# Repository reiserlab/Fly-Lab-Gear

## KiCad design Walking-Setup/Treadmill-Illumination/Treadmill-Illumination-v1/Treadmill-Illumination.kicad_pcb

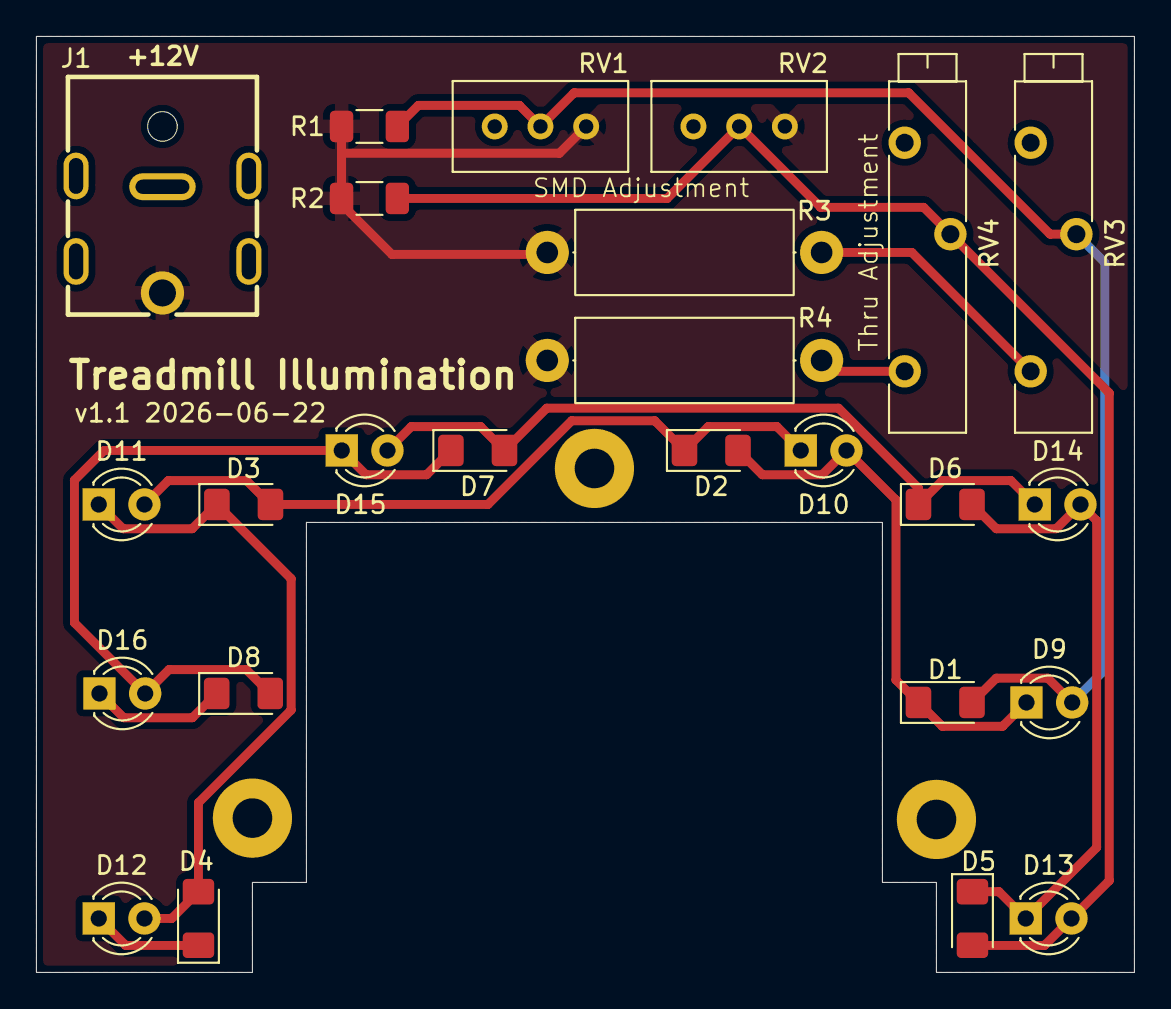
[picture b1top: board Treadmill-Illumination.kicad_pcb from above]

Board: 2 copper layers, 61.0 x 52.0 mm, 28 parts (0 on the bottom side), 12 nets.

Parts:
D1, D2, D3, D4, D5, D6, D7, D8: LED; LED_1206_3216Metric_Pad1.42x1.75mm_HandSolder
D9, D10, D11, D12, D13, D14, D15, D16: LED; LED_D3.0mm
H1, H2, H3: MountingHole_Pad; MountingHole_2.2mm_M2_Pad
J1: Barrel_Jack_MountingPin; DC-IN-TH_DC-053D-20A
R1, R2: 1k; R_1206_3216Metric_Pad1.30x1.75mm_HandSolder
R3, R4: 120; R_Axial_DIN0414_L11.9mm_D4.5mm_P15.24mm_Horizontal
RV1, RV2: R_Potentiometer; Potentiometer_Bourns_3386C_Horizontal
RV3, RV4: R_Potentiometer; Potentiometer_Bourns_3005_Horizontal

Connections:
+12V: J1.1, R1.1, R2.1, R3.1, R4.1, RV1.1, RV2.1
GND: D4.1 (K), D8.1 (K), D12.1 (K), D16.1 (K), H1.1 (1_1), H2.1 (1_1), H3.1 (1_1), J1.2, RV1.3, RV2.3, RV3.3, RV4.3
unnamed: D1.2 (A), D9.2 (A), R1.2, RV1.2, RV3.2
unnamed: D1.1 (K), D2.2 (A), D9.1 (K), D10.2 (A)
unnamed: D2.1 (K), D3.2 (A), D10.1 (K), D11.2 (A)
unnamed: D3.1 (K), D4.2 (A), D11.1 (K), D12.2 (A)
unnamed: D5.2 (A), D13.2 (A), R2.2, RV2.2, RV4.2
unnamed: D5.1 (K), D6.2 (A), D13.1 (K), D14.2 (A)
unnamed: D6.1 (K), D7.2 (A), D14.1 (K), D15.2 (A)
unnamed: D7.1 (K), D8.2 (A), D15.1 (K), D16.2 (A)
unnamed: R3.2, RV3.1
unnamed: R4.2, RV4.1
